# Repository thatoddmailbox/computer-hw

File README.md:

# computer-hw
Hardware for the Soviet-era microcomputer I built. See [this repository](https://github.com/thatoddmailbox/computer) for more information.

Most of the files in this respository are in KiCad format and require KiCad 4.0.7 to view; however, if you just want to view the schematic, you can find a PDF version in the doc folder or linked in the list below.

## Helpful documentation
* [Schematic in PDF format](./doc/schematic.pdf)
* [Original plan for memory decoding](./doc/decoding_original_plan.jpeg)
* [Changes to memory decoding when ROM and RAM chips didn't work](./doc/decoding_workaround.jpeg)
* [High-quality mechanical drawing for ZIF socket](./doc/zif_mechanical_drawing.jpeg)

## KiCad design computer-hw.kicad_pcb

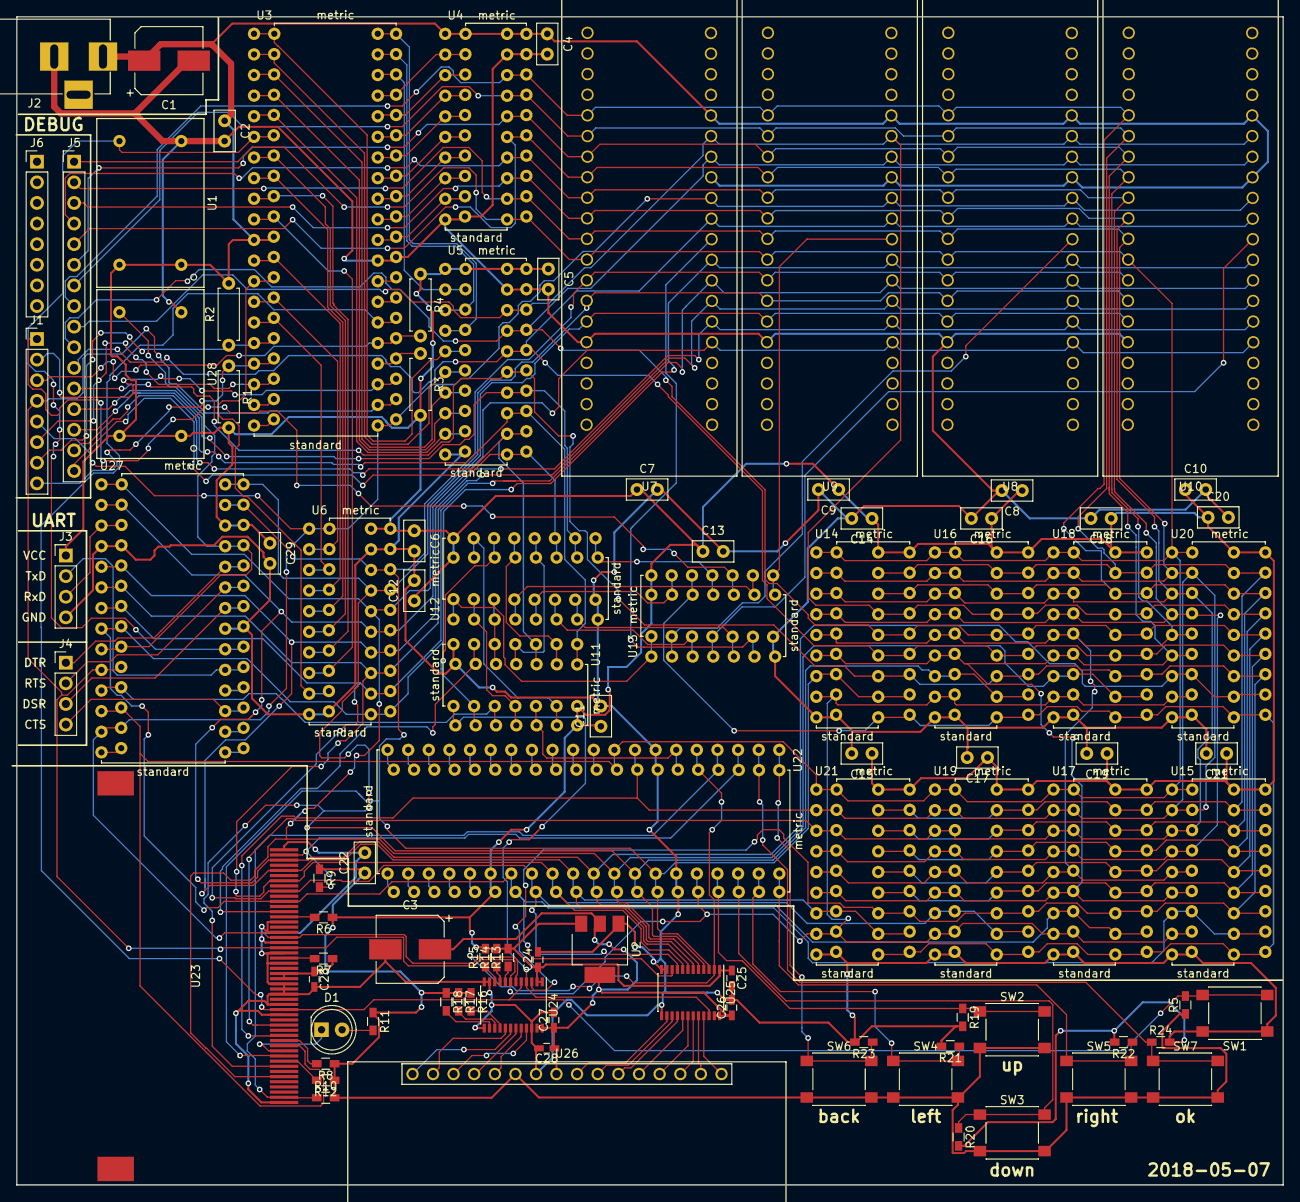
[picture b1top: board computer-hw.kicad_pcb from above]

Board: 2 copper layers, 156.0 x 143.9 mm, 95 parts (0 on the bottom side), 123 nets.

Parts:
C1, C3: 1000 uF; CP_Elec_8x10
C2, C4, C5, C6, C7, C8, C9, C10, C11, C12, C13, C14, C15, C16, C17, C18, C19, C20, C21, C22, C29: 0.1uF; C_Disc_D5.0mm_W2.5mm_P2.50mm
C23, C24, C25, C26, C27, C28: 0.1uF; C_0603_HandSoldering
D1: LED; LED_D5.0mm
J1, J6: Conn_01x08; Pin_Header_Straight_1x08_Pitch2.54mm
J2: Barrel_Jack; BARREL_JACK
J3, J4: Conn_01x04; Pin_Header_Straight_1x04_Pitch2.54mm
J5: Conn_01x16; Pin_Header_Straight_1x16_Pitch2.54mm
R1, R2, R3, R4: 10k; R_Axial_DIN0207_L6.3mm_D2.5mm_P7.62mm_Horizontal
R5, R6, R7, R8, R9, R10, R11, R12, R13, R14, R15, R16, R17, R18, R19, R20, R21, R22, R23, R24: 10k; R_0603_HandSoldering
SW1: SW_Push; SW_SPST_PTS645
SW2: B_UP; SW_SPST_PTS645
SW3: B_DOWN; SW_SPST_PTS645
SW4: B_LEFT; SW_SPST_PTS645
SW5: B_RIGHT; SW_SPST_PTS645
SW6: B_BACK; SW_SPST_PTS645
SW7: B_OK; SW_SPST_PTS645
U1: 2 MHz; OSC
U2: AP1117-33; SOT-223-3_TabPin2
U3: Z80CPU; HYBRID_DIP40
U4, U5, U6: 74HC245; HYBRID_DIP20
U7, U8, U9, U10: 2716; ZIF40_DIP24
U11, U13: 74LS04; HYBRID_DIP14
U12: 4028; HYBRID_DIP16
U14, U15, U16, U17, U18, U19, U20, U21: KR537RU2; HYBRID_WEIRD_RAM
U22: 8255; HYBRID_DIP40
U23: CF
U24, U25: SN74LVC8T245; TSSOP-24_4.4x7.8mm_Pitch0.65mm
U26: DISPLAY_MOD
U27: KR580VV51A; HYBRID_DIP28
U28: 1.8432 MHz; OSC

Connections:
+3V3: C3.1, C26.1, C27.1, C28.1, U2.2, U24.23, U24.24, U25.23, U25.24, U26.9
/A0: J5.1, U4.11, U7.8, U8.8, U9.8, U10.8, U14.1, U15.1, U16.1, U17.1, U18.1, U19.1, U20.1, U21.1, U22.9, U23.20, U27.12
/A1: J5.2, U4.12, U7.7, U8.7, U9.7, U10.7, U14.2, U15.2, U16.2, U17.2, U18.2, U19.2, U20.2, U21.2, U22.8, U23.19
/A2: J5.3, U4.13, U7.6, U8.6, U9.6, U10.6, U14.3, U15.3, U16.3, U17.3, U18.3, U19.3, U20.3, U21.3, U23.18
/A3: J5.4, U4.14, U7.5, U8.5, U9.5, U10.5, U14.4, U15.4, U16.4, U17.4, U18.4, U19.4, U20.4, U21.4
/A4: J5.5, U4.15, U7.4, U8.4, U9.4, U10.4, U14.5, U15.5, U16.5, U17.5, U18.5, U19.5, U20.5, U21.5
/A5: J5.6, U4.16, U7.3, U8.3, U9.3, U10.3, U14.6, U15.6, U16.6, U17.6, U18.6, U19.6, U20.6, U21.6
/A6: J5.7, U4.17, U7.2, U8.2, U9.2, U10.2, U14.17, U15.17, U16.17, U17.17, U18.17, U19.17, U20.17, U21.17
/A7: J5.8, U4.18, U7.1, U8.1, U9.1, U10.1, U14.16, U15.16, U16.16, U17.16, U18.16, U19.16, U20.16, U21.16
/A8: J5.9, U5.18, U7.23, U8.23, U9.23, U10.23, U14.15, U15.15, U16.15, U17.15, U18.15, U19.15, U20.15, U21.15
/A9: J5.10, U5.17, U7.22, U8.22, U9.22, U10.22, U14.14, U15.14, U16.14, U17.14, U18.14, U19.14, U20.14, U21.14
/A10: J5.11, U5.16, U7.19, U8.19, U9.19, U10.19, U14.13, U15.13, U16.13, U17.13, U18.13, U19.13, U20.13, U21.13
/A11: J5.12, U5.15, U14.12, U15.12, U16.12, U17.12, U18.12, U19.12, U20.12, U21.12, U24.3
/Buttons/PA2: R24.1, SW7.1, U22.2
/Buttons/PA3: R23.1, SW6.1, U22.1
/Buttons/PA4: R22.1, SW5.1, U22.40
/Buttons/PA5: R21.1, SW4.1, U22.39
/Buttons/PA6: R20.1, SW3.1, U22.38
/Buttons/PA7: R19.1, SW2.1, U22.37
/CompactFlash//CF_EN: U11.6, U23.7
/D0: U6.18, U7.9, U8.9, U9.9, U10.9, U14.7, U14.11, U22.34, U23.21, U25.3, U27.27
/D1: U6.17, U7.10, U8.10, U9.10, U10.10, U16.7, U16.11, U22.33, U23.22, U25.4, U27.28
/D2: U6.16, U7.11, U8.11, U9.11, U10.11, U18.7, U18.11, U22.32, U23.23, U25.5, U27.1
/D3: U6.15, U7.13, U8.13, U9.13, U10.13, U20.7, U20.11, U22.31, U23.2, U25.6, U27.2
/D4: U6.14, U7.14, U8.14, U9.14, U10.14, U21.7, U21.11, U22.30, U23.3, U25.7, U27.5
/D5: U6.13, U7.15, U8.15, U9.15, U10.15, U19.7, U19.11, U22.29, U23.4, U25.8, U27.6
/D6: U6.12, U7.16, U8.16, U9.16, U10.16, U17.7, U17.11, U22.28, U23.5, U25.9, U27.7
/D7: U6.11, U7.17, U8.17, U9.17, U10.17, U15.7, U15.11, U22.27, U23.6, U25.10, U27.8
/Decoding//DISPLAY_EN: U11.8, U24.4, U25.22
/Decoding//PIO_EN: U11.12, U22.6
/Decoding//RAM_EN: U13.12, U14.10, U15.10, U16.10, U17.10, U18.10, U19.10, U20.10, U21.10
/Decoding//ROM0_EN: U7.18, U13.6
/Decoding//ROM1_EN: U9.18, U13.8
/Decoding//ROM2_EN: U8.18, U13.2
/Decoding//ROM3_EN: U10.18, U13.4
/Decoding//UART_EN: U11.10, U27.11
/EXP_EN: J1.1, U13.10
/PA0: R10.1, U22.4, U23.25
/PA1: R9.2, U22.3, U23.26
/RD: J1.5, U3.21, U6.1, U7.20, U8.20, U9.20, U10.20, U22.5, U23.34, U24.6, U25.2, U27.13
/RESET: R5.2, SW1.2, U3.26, U23.41, U24.5
/UART//CTS: J4.4, U27.17
/UART//DSR: J4.3, U27.22
/UART//DTR: J4.1, U27.24
/UART//RTS: J4.2, U27.23
/UART/RxD: J3.3, U27.3
/UART/TxD: J3.2, U27.19
/WR: J1.4, U3.22, U14.8, U15.8, U16.8, U17.8, U18.8, U19.8, U20.8, U21.8, U22.36, U23.35, U24.7, U27.10
A12: J5.13, U5.14, U12.10
A13: J5.14, U5.13, U11.1
A14: J5.15, U5.12, U11.3
A15: J5.16, U5.11, U12.11
CLK: U1.8, U3.6, U27.20
GND: C1.2, C2.2, C3.2, C4.2, C5.2, C6.2, C7.2, C8.2, C9.2, C10.2, C11.2, C12.2, C13.2, C14.2, C15.2, C16.2, C17.2, C18.2, C19.2, C20.2, C21.2, C22.2, C23.2, C24.2, C25.2, C26.2, C27.2, C28.2, C29.2, J2.2, J3.4, R19.2, R20.2, R21.2, R22.2, R23.2, R24.2, SW1.1, U1.7, U2.1, U3.29, U4.10, U4.19, U5.10, U5.19, U6.10, U6.19, U7.12, U8.12, U9.12, U10.12, U11.7, U12.8, U13.7, U14.9, U15.9, U16.9, U17.9, U18.9, U19.9, U20.9, U21.9, U22.7, U22.35, U23.1, U23.8, U23.9, U23.10, U23.11, U23.12, U23.14, U23.15, U23.16, U23.17, U23.39, U23.50, U24.11, U24.12, U24.13, U24.22, U25.11, U25.12, U25.13, U26.10, U27.4, U27.21, U28.7
unnamed: D1.1, U23.45
unnamed: D1.2, R11.2
unnamed: J1.2, U3.23
unnamed: J1.3, R4.2, U3.25
unnamed: J1.6, U3.18
unnamed: J1.7, R2.1, U3.16
unnamed: J1.8, R1.1, U3.17
unnamed: R3.1, U3.24
unnamed: R6.2, U23.32
unnamed: R7.2, U23.36
unnamed: R8.2, U23.44
unnamed: R12.2, U23.46
unnamed: R13.1, U24.8
unnamed: R14.1, U24.9
unnamed: R15.1, U24.10
unnamed: R16.2, U24.16
unnamed: R17.2, U24.15
unnamed: R18.2, U24.14
unnamed: U3.1, U5.5
unnamed: U3.2, U5.6
unnamed: U3.3, U5.7
unnamed: U3.4, U5.8
unnamed: U3.5, U5.9
unnamed: U3.7, U6.6
unnamed: U3.8, U6.5
unnamed: U3.9, U6.7
unnamed: U3.10, U6.8
unnamed: U3.12, U6.4
unnamed: U3.13, U6.9
unnamed: U3.14, U6.2
unnamed: U3.15, U6.3
unnamed: U3.30, U4.9
unnamed: U3.31, U4.8
unnamed: U3.32, U4.7
unnamed: U3.33, U4.6
unnamed: U3.34, U4.5
unnamed: U3.35, U4.4
unnamed: U3.36, U4.3
unnamed: U3.37, U4.2
unnamed: U3.38, U5.2
unnamed: U3.39, U5.3
unnamed: U3.40, U5.4
unnamed: U11.2, U12.13
unnamed: U11.4, U12.12
unnamed: U11.5, U12.3
unnamed: U11.9, U12.14
unnamed: U11.11, U12.2
unnamed: U11.13, U12.15
unnamed: U12.1, U13.1
unnamed: U12.4, U13.9
unnamed: U12.5, U13.13
unnamed: U12.6, U13.3
unnamed: U12.7, U13.5
unnamed: U12.9, U13.11
unnamed: U24.17, U26.15
unnamed: U24.18, U26.16
unnamed: U24.19, U26.13
unnamed: U24.20, U26.12
unnamed: U24.21, U26.14
unnamed: U25.14, U26.8
unnamed: U25.15, U26.7
unnamed: U25.16, U26.6
unnamed: U25.17, U26.5
unnamed: U25.18, U26.4
unnamed: U25.19, U26.3
unnamed: U25.20, U26.2
unnamed: U25.21, U26.1
unnamed: U27.9, U27.25, U28.8
VCC: C1.1, C2.1, C4.1, C5.1, C6.1, C7.1, C8.1, C9.1, C10.1, C11.1, C12.1, C13.1, C14.1, C15.1, C16.1, C17.1, C18.1, C19.1, C20.1, C21.1, C22.1, C23.1, C24.1, C25.1, C29.1, J2.1, J3.1, R1.2, R2.2, R3.2, R4.1, R5.1, R6.1, R7.1, R8.1, R9.1, R10.2, R11.1, R12.1, R13.2, R14.2, R15.2, R16.1, R17.1, R18.1, SW2.2, SW3.2, SW4.2, SW5.2, SW6.2, SW7.2, U1.1, U1.14, U2.3, U3.11, U4.1, U4.20, U5.1, U5.20, U6.20, U7.21, U7.24, U8.21, U8.24, U9.21, U9.24, U10.21, U10.24, U11.14, U12.16, U13.14, U14.18, U15.18, U16.18, U17.18, U18.18, U19.18, U20.18, U21.18, U22.26, U23.13, U23.38, U24.1, U24.2, U25.1, U26.11, U27.26, U28.1, U28.14

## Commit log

2018-05-25 commit original layout files
2018-05-25 add fixes so that the pcb actually meets the design rules
2018-05-25 add schematic in pdf format
2018-05-25 add helpful notes in jpeg format
2018-05-25 add README
2018-06-07 move documentation into separate folder and add schematic link to readme
2018-06-08 add to readme
2018-06-08 add license
